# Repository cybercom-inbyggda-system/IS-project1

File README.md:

# IS-project1

Simple gaming platform HW and SW

HW developed in KiCad
 - Atmel ATTiny
 - SPI OLED display
 - Buttons
 - Power

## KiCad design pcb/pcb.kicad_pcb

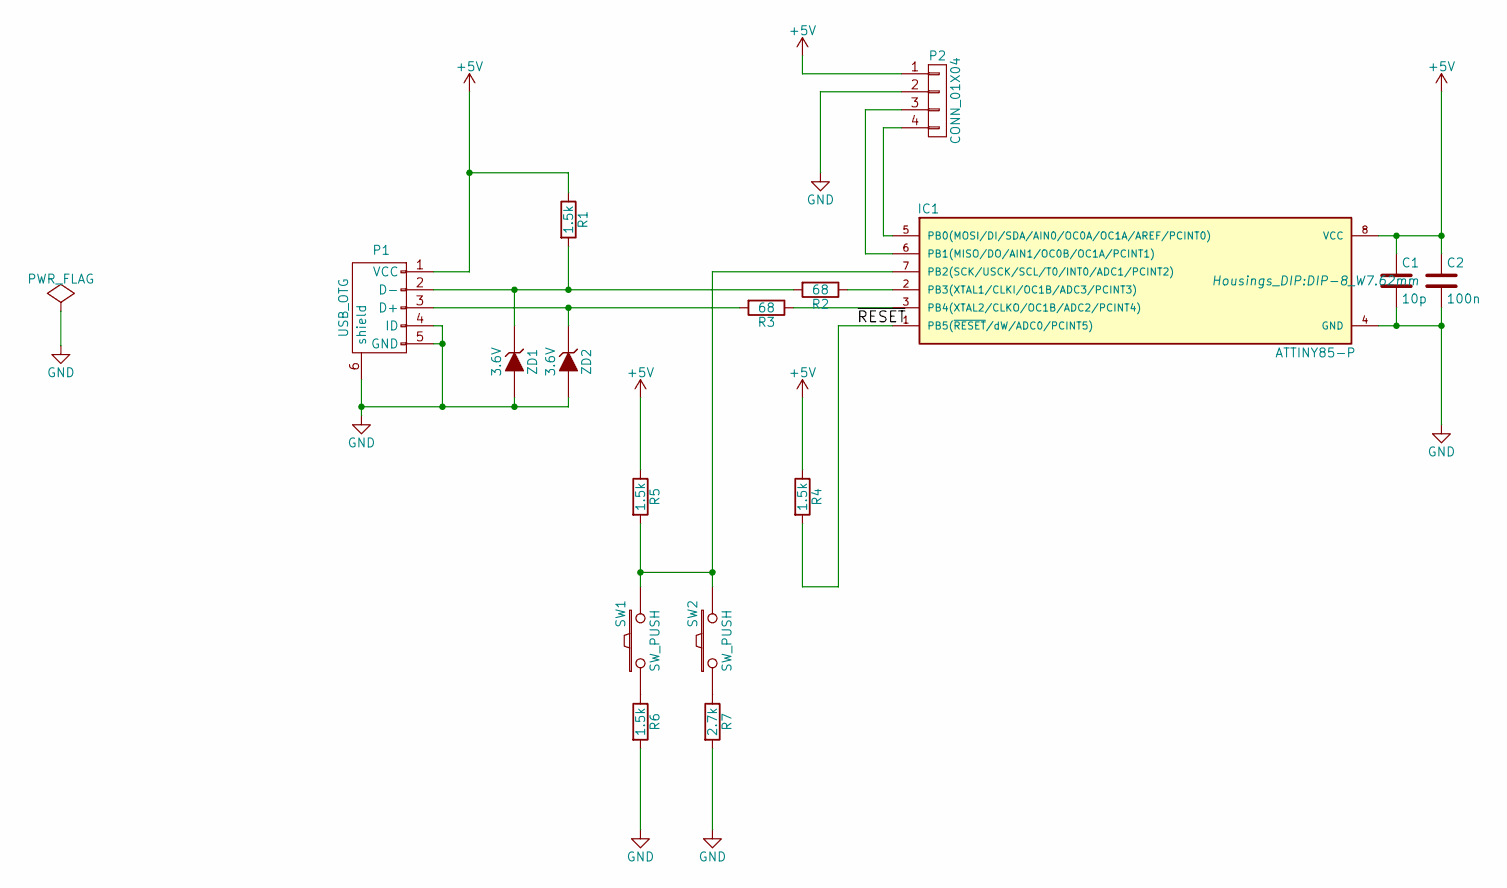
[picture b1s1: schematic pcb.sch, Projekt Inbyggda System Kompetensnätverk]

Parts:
C1: 10p; C_1206_HandSoldering
C2: 100n; C_1206_HandSoldering
IC1: ATTINY85-P; DIP-8_W7.62mm
P1: USB_OTG; USB_Micro-B
P2: CONN_01X04; Socket_Strip_Straight_1x04
R1, R4, R5, R6: 1.5k; R_1206_HandSoldering
R2, R3: 68; R_1206_HandSoldering
R7: 2.7k; R_1206_HandSoldering
SW1, SW2: SW_PUSH; SW_SPST_FSMSM
ZD1, ZD2: 3.6V; SOD-123

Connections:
+5V: C1.1, C2.1, IC1.8 (VCC), P1.1 (VCC), P2.1, R1.1, R4.1, R5.1
/~RESET: IC1.1 (PB5(~RESET~/dW/ADC0/PCINT5)), R4.2
GND: C1.2, C2.2, IC1.4 (GND), P1.4 (ID), P1.5 (GND), P1.6 (shield), P2.2, R6.2, R7.2, ZD1.2 (A), ZD2.2 (A)
unnamed: P1.2 (D-), R1.2, R2.2, ZD1.1 (K)
unnamed: P1.3 (D+), R3.2, ZD2.1 (K)
unnamed: IC1.2 (PB3(XTAL1/CLKI/OC1B/ADC3/PCINT3)), R2.1
unnamed: IC1.3 (PB4(XTAL2/CLKO/OC1B/ADC2/PCINT4)), R3.1
unnamed: IC1.5 (PB0(MOSI/DI/SDA/AIN0/OC0A/OC1A/AREF/PCI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), P2.4
unnamed: IC1.6 (PB1(MISO/DO/AIN1/OC0B/OC1A/PCINT1)), P2.3
unnamed: IC1.7 (PB2(SCK/USCK/SCL/T0/INT0/ADC1/PCINT2)), R5.2, SW1.2, SW2.2
unnamed: R6.1, SW1.1
unnamed: R7.1, SW2.1

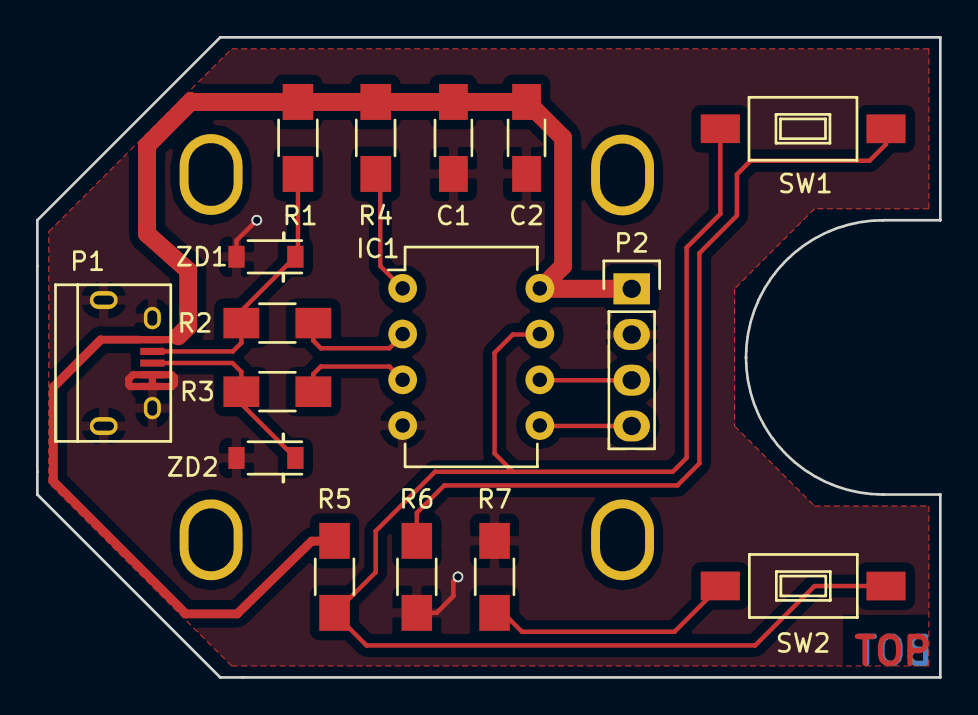
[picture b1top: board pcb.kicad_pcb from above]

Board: 2 copper layers, 50.2 x 35.6 mm, 20 parts (0 on the bottom side), 12 nets.

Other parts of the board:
OH1, OH2, OH3, OH4: 1pin

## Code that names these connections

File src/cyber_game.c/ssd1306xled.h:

/**
 * SSD1306xLED - Drivers for SSD1306 controlled dot matrix OLED/PLED 128x64 displays
 *
 * @created: 2014-08-12
 * @author: Neven Boyanov
 *
 * This is part of the Tinusaur/SSD1306xLED project.
 *
 * Copyright (c) 2016 Neven Boyanov, Tinusaur Team. All Rights Reserved.
 * Distributed as open source software under MIT License, see LICENSE.txt file.
 * Please, as a favor, retain the link http://tinusaur.org to The Tinusaur Project.
 *
 * Source code available at: https://bitbucket.org/tinusaur/ssd1306xled
 *
 */

#ifndef SSD1306XLED_H
#define SSD1306XLED_H

// ============================================================================

#define CYBERCOM_PCB   1
#define BREADBOARD     2
//
// ~~~~~~~~~~~~~~~~~~~~~~~~~~~~~~~~~~~~~~
//                ATtiny
//               25/45/85
//              +-(_)------+
//      (RST)---+ PB5  Vcc +---(+)-------
//           ---+ PB3  PB2 +---
//           ---+ PB4  PB1 +---SCL
// -------(-)---+ GND  PB0 +---SDA
//              +----------+
//
// ~~~~~~~~~~~~~~~~~~~~~~~~~~~~~~~~~~~~~~

#if BOARD == CYBERCOM_PCB
#define SSD1306_SCL    PB1   // SCL on SSD1306 Board
#define SSD1306_SDA    PB0   // SDA on SSD1306 Board
#elif BOARD == BREADBOARD
#define SSD1306_SCL    PB3
#define SSD1306_SDA    PB4
#endif

#define SSD1306_SA     0x78  // Slave address

// ----------------------------------------------------------------------------

// Convenience definitions for PORTB

#define DIGITAL_WRITE_HIGH(PORT) PORTB |= (1 << PORT)
#define DIGITAL_WRITE_LOW(PORT) PORTB &= ~(1 << PORT)

// ----------------------------------------------------------------------------

/**
 * SSD1306xLED - Drivers for SSD1306 controlled dot matrix OLED/PLED 128x64 displays
 *
 * @created: 2014-08-12
 * @author: Neven Boyanov
 *
 * This is part of the Tinusaur/SSD1306xLED project.
 *
 * Copyright (c) 2016 Neven Boyanov, Tinusaur Team. All Rights Reserved.
 * Distributed as open source software under MIT License, see LICENSE.txt file.
 * Please, as a favor, retain the link http://tinusaur.org to The Tinusaur Project.
 *
 * Source code available at: https://bitbucket.org/tinusaur/ssd1306xled
 *
 */

// ============================================================================

#include <stdlib.h>
#include <avr/io.h>

#include <stdint.h>
#include <avr/io.h>

#include <avr/pgmspace.h>

// ----------------------------------------------------------------------------

// Some code based on "IIC_wtihout_ACK" by http://www.14blog.com/archives/1358

const uint8_t ssd1306_init_sequence [] PROGMEM = {  // Initialization Sequence
  0xAE,       // Display OFF (sleep mode)
  0x20, 0b00, // Set Memory Addressing Mode
              // 00=Horizontal Addressing Mode; 01=Vertical Addressing Mode;
              // 10=Page Addressing Mode (RESET); 11=Invalid
  0xB0,       // Set Page Start Address for Page Addressing Mode, 0-7
  0xC8,       // Set COM Output Scan Direction
  0x00,       // ---set low column address
  0x10,       // ---set high column address
  0x40,       // --set start line address
  0x81, 0x3F, // Set contrast control register
  0xA1,       // Set Segment Re-map. A0=address mapped; A1=address 127 mapped. 
  0xA6,       // Set display mode. A6=Normal; A7=Inverse
  0xA8, 0x3F, // Set multiplex ratio(1 to 64)
  0xA4,       // Output RAM to Display
              // 0xA4=Output follows RAM content; 0xA5,Output ignores RAM content
  0xD3, 0x00, // Set display offset. 00 = no offset
  0xD5,       // --set display clock divide ratio/oscillator frequency
  0xF0,       // --set divide ratio
  0xD9, 0x22, // Set pre-charge period
  0xDA, 0x12, // Set com pins hardware configuration    
  0xDB,       // --set vcomh
  0x20,       // 0x20,0.77xVcc
  0x8D, 0x14, // Set DC-DC enable
  0xAF        // Display ON in normal mode
  
};

// ----------------------------------------------------------------------------

void ssd1306_xfer_start(void)
{
  DIGITAL_WRITE_HIGH(SSD1306_SCL);  // Set to HIGH
  DIGITAL_WRITE_HIGH(SSD1306_SDA);  // Set to HIGH
  DIGITAL_WRITE_LOW(SSD1306_SDA);   // Set to LOW
  DIGITAL_WRITE_LOW(SSD1306_SCL);   // Set to LOW
}

void ssd1306_xfer_stop(void)
{
  DIGITAL_WRITE_LOW(SSD1306_SCL);   // Set to LOW
  DIGITAL_WRITE_LOW(SSD1306_SDA);   // Set to LOW
  DIGITAL_WRITE_HIGH(SSD1306_SCL);  // Set to HIGH
  DIGITAL_WRITE_HIGH(SSD1306_SDA);  // Set to HIGH
}

void ssd1306_send_byte(uint8_t byte)
{
  uint8_t i;
  for (i = 0; i < 8; i++)
  {
    if ((byte << i) & 0x80)
      DIGITAL_WRITE_HIGH(SSD1306_SDA);
    else
      DIGITAL_WRITE_LOW(SSD1306_SDA);
    
    DIGITAL_WRITE_HIGH(SSD1306_SCL);
    DIGITAL_WRITE_LOW(SSD1306_SCL);
  }
  DIGITAL_WRITE_HIGH(SSD1306_SDA);
  DIGITAL_WRITE_HIGH(SSD1306_SCL);
  DIGITAL_WRITE_LOW(SSD1306_SCL);
}

void ssd1306_send_command_start(void) {
  ssd1306_xfer_start();
  ssd1306_send_byte(SSD1306_SA);  // Slave address, SA0=0
  ssd1306_send_byte(0x00);  // write command
}

void ssd1306_send_command_stop(void) {
  ssd1306_xfer_stop();
}

void ssd1306_send_command(uint8_t command)
{
  ssd1306_send_command_start();
  ssd1306_send_byte(command);
  ssd1306_send_command_stop();
}

void ssd1306_send_data_start(void)
{
  ssd1306_xfer_start();
  ssd1306_send_byte(SSD1306_SA);
  ssd1306_send_byte(0x40);  //write data
}

void ssd1306_send_data_stop(void)
{
  ssd1306_xfer_stop();
}

void ssd1306_init(void)
{
  DDRB |= (1 << SSD1306_SDA); // Set port as output
  DDRB |= (1 << SSD1306_SCL); // Set port as output
  
  for (uint8_t i = 0; i < sizeof (ssd1306_init_sequence); i++) {
    ssd1306_send_command(pgm_read_byte(&ssd1306_init_sequence[i]));
  }
}

void ssd1306_setpos(uint8_t x, uint8_t y)
{
  ssd1306_send_command_start();
  ssd1306_send_byte(0xb0 + y);
  ssd1306_send_byte(((x & 0xf0) >> 4) | 0x10); // | 0x10
/* TODO: Verify correctness */  ssd1306_send_byte((x & 0x0f)); // | 0x01
  ssd1306_send_command_stop();
}


#endif

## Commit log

2016-04-27 First revision of HW
2016-05-06 Modified button layout
2016-05-06 Removed backup file from repo
2016-07-09 Added ignore filter.
2016-07-09 Updated readme.
2016-11-13 Removed warnings in Electrical Rules Checker
2016-11-19 Created board layout in Pcbnew
2016-11-19 Remove unused display lib
2016-11-20 Minor changes for production
2016-11-20 Sorting misc files into new directories
2016-11-20 Same design (in kicad) as found in gerber files
2016-12-02 Added photo of PCB
2017-06-26 Added images
2017-06-26 Implemented tool for image conversion
2017-06-26 First draft program
